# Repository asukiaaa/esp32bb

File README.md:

# ESP32BB
A kicad project for ESP-WROOM-32 and breadboard.

[schema](/docs/esp32bb.pdf)

# Driver
This board uses CP2102 for serial communication.
For mac and windiws user, please install the following driver.
Linux supports cp2102 defaul, so linux user does not need any driver.

[CP210x USB to UART Bridge VCP Drivers](http://www.silabs.com/products/development-tools/software/usb-to-uart-bridge-vcp-drivers)

# Shop
[trial stacks](https://trialstacks.base.ec/items/6243312)

# Components
- [esp-wroop-32](http://akizukidenshi.com/catalog/g/gM-11647/)
- [Hirose-microB-USB](http://akizukidenshi.com/catalog/g/gC-05254/)
- [Diode](http://akizukidenshi.com/catalog/g/gI-05951/)
- [transistor MMBT3904](http://akizukidenshi.com/catalog/g/gI-05969/)
- [switch SKRPACE010](http://akizukidenshi.com/catalog/g/gP-06185/)
- [100uf 1206 condensor](http://akizukidenshi.com/catalog/g/gP-08260/)
- [10uf 0603 condensor](http://akizukidenshi.com/catalog/g/gP-07768/)
- [0.1uf 0603 condensor](http://akizukidenshi.com/catalog/g/gP-04940/)
- [1nf (1000pf) 0603 condensor](http://akizukidenshi.com/catalog/g/gP-09285/)
- [10k 0603 registor](http://akizukidenshi.com/catalog/g/gR-06103/)
- [led](http://akizukidenshi.com/catalog/g/gI-06417/)
- [Pin socket](http://akizukidenshi.com/catalog/g/gC-05779/)
- Bread board: [akizuki](http://akizukidenshi.com/catalog/g/gP-05158/) or [aliexpress](https://www.aliexpress.com/item/SYB-170-Mini-Prototype-Experiment-Test-Breadboard-Board-Tie-points-170-Tie-points-35-47-8/32595538101.html?spm=2114.13010608.0.0.nAnEqS)
- [CP2102](https://www.aliexpress.com/item/5pcs-Free-shipping-SILABS-CP2102-GMR-CP2102-QFN-28-offen-use-laptop-chip-100-new-original/32503317767.html?spm=2114.13010608.0.0.PUEIRm)
- [NCP1117ST33T3G](https://www.aliexpress.com/item/Free-Shipping-NCP1117ST33T3G-NCP1117-3-3V-linear-regulator-SOT-223-package/32244660148.html?spm=2114.13010608.0.0.PUEIRm)

# Footprints
- [ESP32-kiCAD-Footprints](https://github.com/adamjvr/ESP32-kiCAD-Footprints)
- [switch: SKRPACE010.kicad_mod](https://github.com/nosuz/kicad-lib/blob/master/module.pretty/SKRPACE010.kicad_mod)

# Programming software tools
ESP32BB is a ESP-WROOM-32 breakout board so you can write your own program by usinig the following tools.

- [espressif/arduino-esp32](https://github.com/espressif/arduino-esp32)
- [espressif/esp-idf](https://github.com/espressif/esp-idf)
- [Mongoose OS](https://mongoose-os.com/)

# License
MIT

# References
- [ESP32-Core-Board-V2_sch.pdf](http://akizukidenshi.com/download/ds/espressifsystems/ESP32-Core-Board-V2_sch.pdf)
- [esp_wroom_32_datasheet_en.pdf](https://espressif.com/sites/default/files/documentation/esp_wroom_32_datasheet_en.pdf)
- [Enginursday: First Impressions of the ESP32](https://www.sparkfun.com/news/2017)
- [ESP32 Development Board with TELEC Memorial photograph](https://macsbug.wordpress.com/2016/12/12/esp32-development-board-with-telec-memorial-photograph/)
- [DS_FT232R](http://www.ftdichip.com/Support/Documents/DataSheets/ICs/DS_FT232R.pdf)
- [SparkFun FTDI Basic Breakout - 3.3V](https://www.sparkfun.com/products/9873)
- [Sehematic of SparkFun FTDI Basic Breakout - 3.3V](http://cdn.sparkfun.com/datasheets/BreakoutBoards/FTDI%20Basic-v22-3.3V.pdf)
- [esp32-thing.sch](https://cdn.sparkfun.com/assets/learn_tutorials/5/0/7/esp32-thing-schematic.pdf)
- [The Internet of Things with ESP32](http://esp32.net/)
- [ESP-WROVER-KIT_SCH-2.pdf](https://dl.espressif.com/dl/schematics/ESP-WROVER-KIT_SCH-2.pdf)
- [ESP32-EVB_Rev_A.pdf](https://github.com/OLIMEX/ESP32-EVB/blob/master/HARDWARE/REV-A/ESP32-EVB_Rev_A.pdf)

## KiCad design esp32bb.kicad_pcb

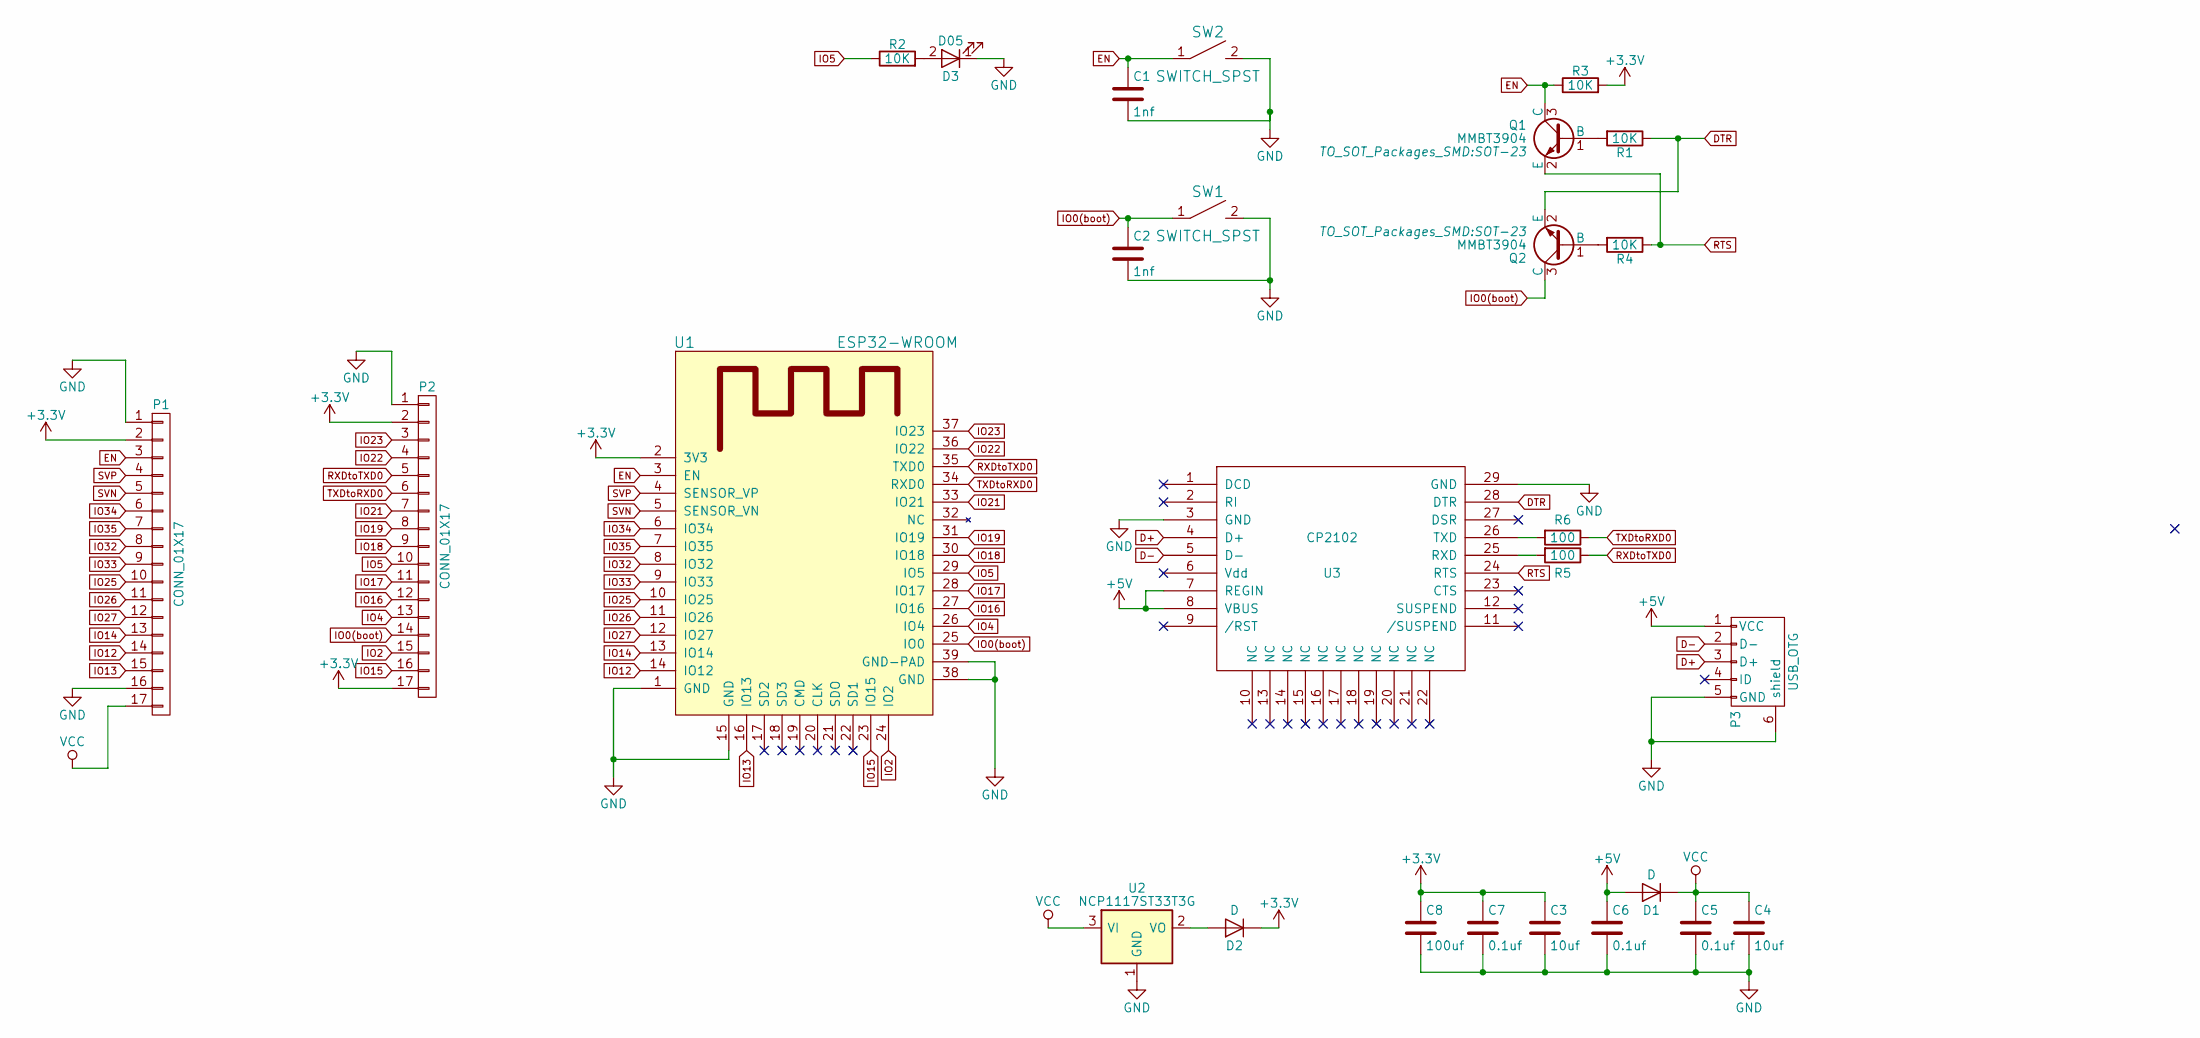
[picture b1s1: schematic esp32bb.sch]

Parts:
C1, C2: 1nf; C_0603
C3, C4: 10uf; C_0603
C5, C6, C7: 0.1uf; C_0603
C8: 100uf; C_1206
D1, D2: D; D_0805
D3: D05; LED_0603
P1, P2: CONN_01X17; Pin_Header_Straight_1x17_Pitch2.54mm
P3: USB_OTG; USB_MICRO_B-HIROSE-ZX62R-B-5P
Q1, Q2: MMBT3904; SOT-23
R1, R2, R3, R4: 10K; R_0603
R5, R6: 100; R_0603
SW1, SW2: SWITCH_SPST; SKRPACE010
U1: ESP32-WROOM
U2: NCP1117ST33T3G; SOT-223
U3: CP2102; QFN-28-1EP_5x5mm_Pitch0.5mm

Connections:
+3V3: C3.1, C7.1, C8.1, D2.1 (K), P1.2, P2.2, P2.17, R3.2, U1.2 (3V3)
+5V: C6.1, D1.2 (A), P3.1 (VCC), U3.7 (REGIN), U3.8 (VBUS); also elsewhere on the board
D+: P3.3 (D+), U3.4 (D+); also elsewhere on the board
D-: P3.2 (D-), U3.5 (D-); also elsewhere on the board
DTR: Q2.2 (E), R1.1, U3.28 (DTR)
EN: C1.1, P1.3, Q1.3 (C), R3.1, SW2.1, U1.3 (EN)
GND: C1.2, C2.2, C3.2, C4.2, C5.2, C6.2, C7.2, C8.2, D3.1 (K), P1.1, P1.16, P2.1, P3.5 (GND), P3.6 (shield), SW1.2, SW2.2, U1.1 (GND), U1.15 (GND), U1.38 (GND), U1.39 (GND-PAD), U2.1 (GND), U3.3 (GND), U3.29 (GND); also elsewhere on the board
IO0(boot): C2.1, P2.14, Q2.3 (C), SW1.1, U1.25 (IO0)
IO2: P2.15, U1.24 (IO2)
IO4: P2.13, U1.26 (IO4)
IO5: P2.10, R2.1, U1.29 (IO5)
IO12: P1.14, U1.14 (IO12)
IO13: P1.15, U1.16 (IO13)
IO14: P1.13, U1.13 (IO14)
IO15: P2.16, U1.23 (IO15)
IO16: P2.12, U1.27 (IO16)
IO17: P2.11, U1.28 (IO17)
IO18: P2.9, U1.30 (IO18)
IO19: P2.8, U1.31 (IO19)
IO21: P2.7, U1.33 (IO21)
IO22: P2.4, U1.36 (IO22)
IO23: P2.3, U1.37 (IO23)
IO25: P1.10, U1.10 (IO25)
IO26: P1.11, U1.11 (IO26)
IO27: P1.12, U1.12 (IO27)
IO32: P1.8, U1.8 (IO32)
IO33: P1.9, U1.9 (IO33)
IO34: P1.6, U1.6 (IO34)
IO35: P1.7, U1.7 (IO35)
unnamed: D2.2 (A), U2.2 (VO)
unnamed: D3.2 (A), R2.2
unnamed 31: P3.4 (ID); also elsewhere on the board
unnamed: Q1.1 (B), R1.2
unnamed: Q2.1 (B), R4.2
unnamed: R5.2, U3.25 (RXD)
unnamed: R6.2, U3.26 (TXD)
RTS: Q1.2 (E), R4.1, U3.24 (RTS)
RXDtoTXD0: P2.5, R5.1, U1.35 (TXD0)
SVN: P1.5, U1.5 (SENSOR_VN)
SVP: P1.4, U1.4 (SENSOR_VP)
TXDtoRXD0: P2.6, R6.1, U1.34 (RXD0)
VCC: C4.1, C5.1, D1.1 (K), P1.17, U2.3 (VI)

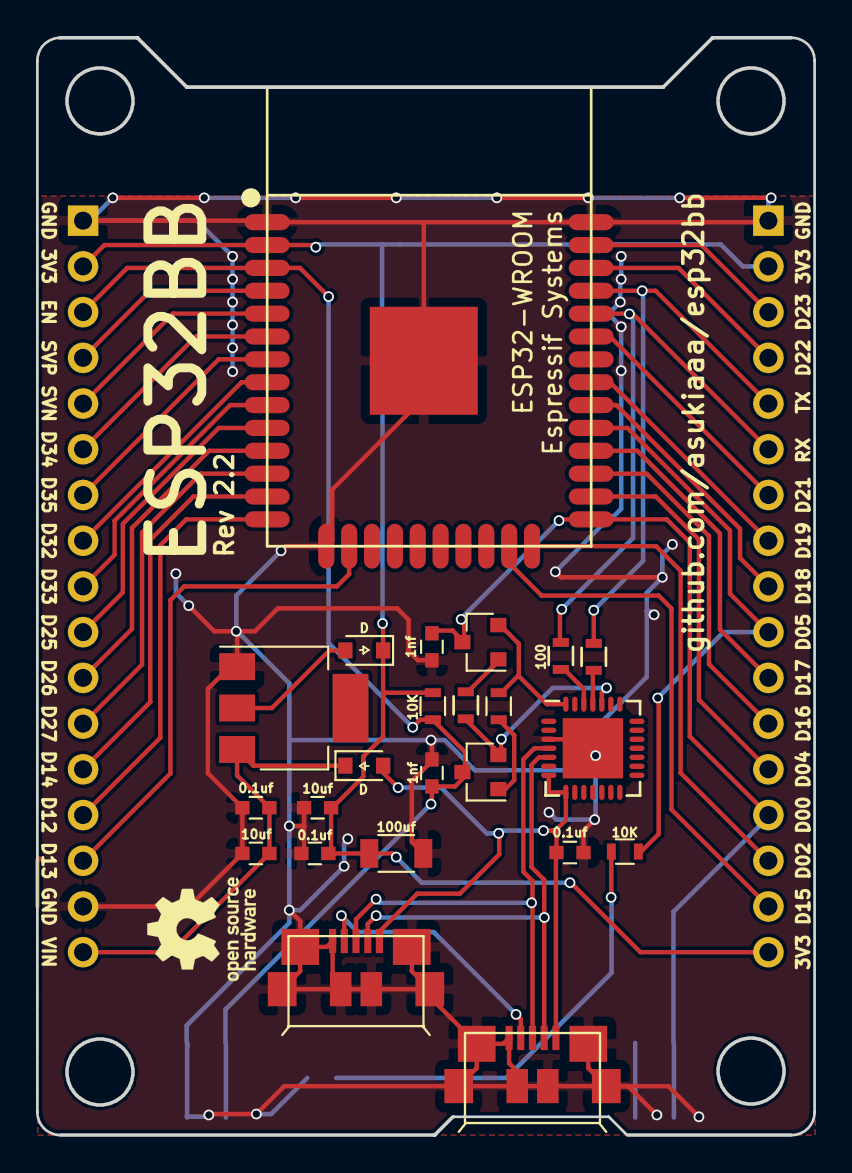
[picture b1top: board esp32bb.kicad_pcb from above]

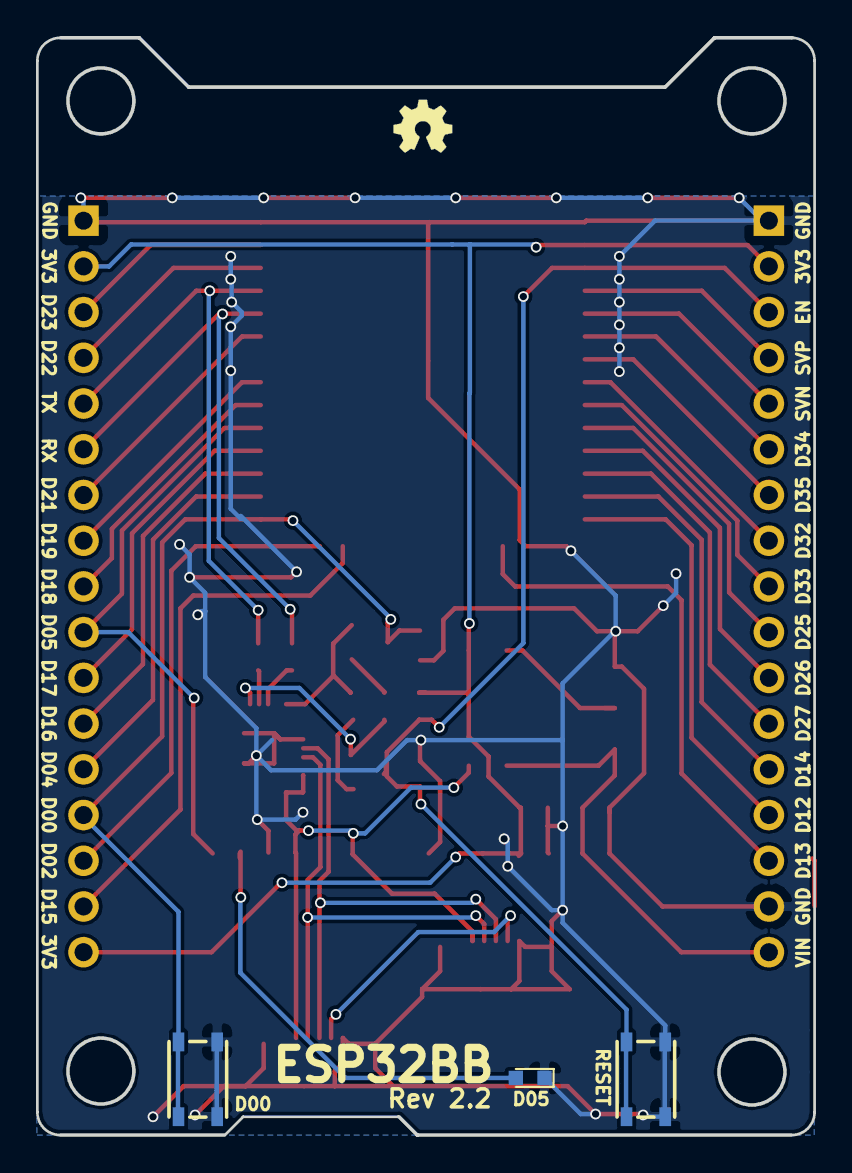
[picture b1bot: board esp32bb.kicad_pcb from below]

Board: 2 copper layers, 43.1 x 61.0 mm, 28 parts (5 on the bottom side), 42 nets.

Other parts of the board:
P3#2: USB_OTG; USB_MICRO_B-HIROSE-ZX62R-B-5P

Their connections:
+5V: P3#2.1; also elsewhere on the board
D+: P3#2.3; also elsewhere on the board
D-: P3#2.2; also elsewhere on the board
GND: P3#2.5, P3#2.6; also elsewhere on the board
unnamed 31: P3#2.4; also elsewhere on the board

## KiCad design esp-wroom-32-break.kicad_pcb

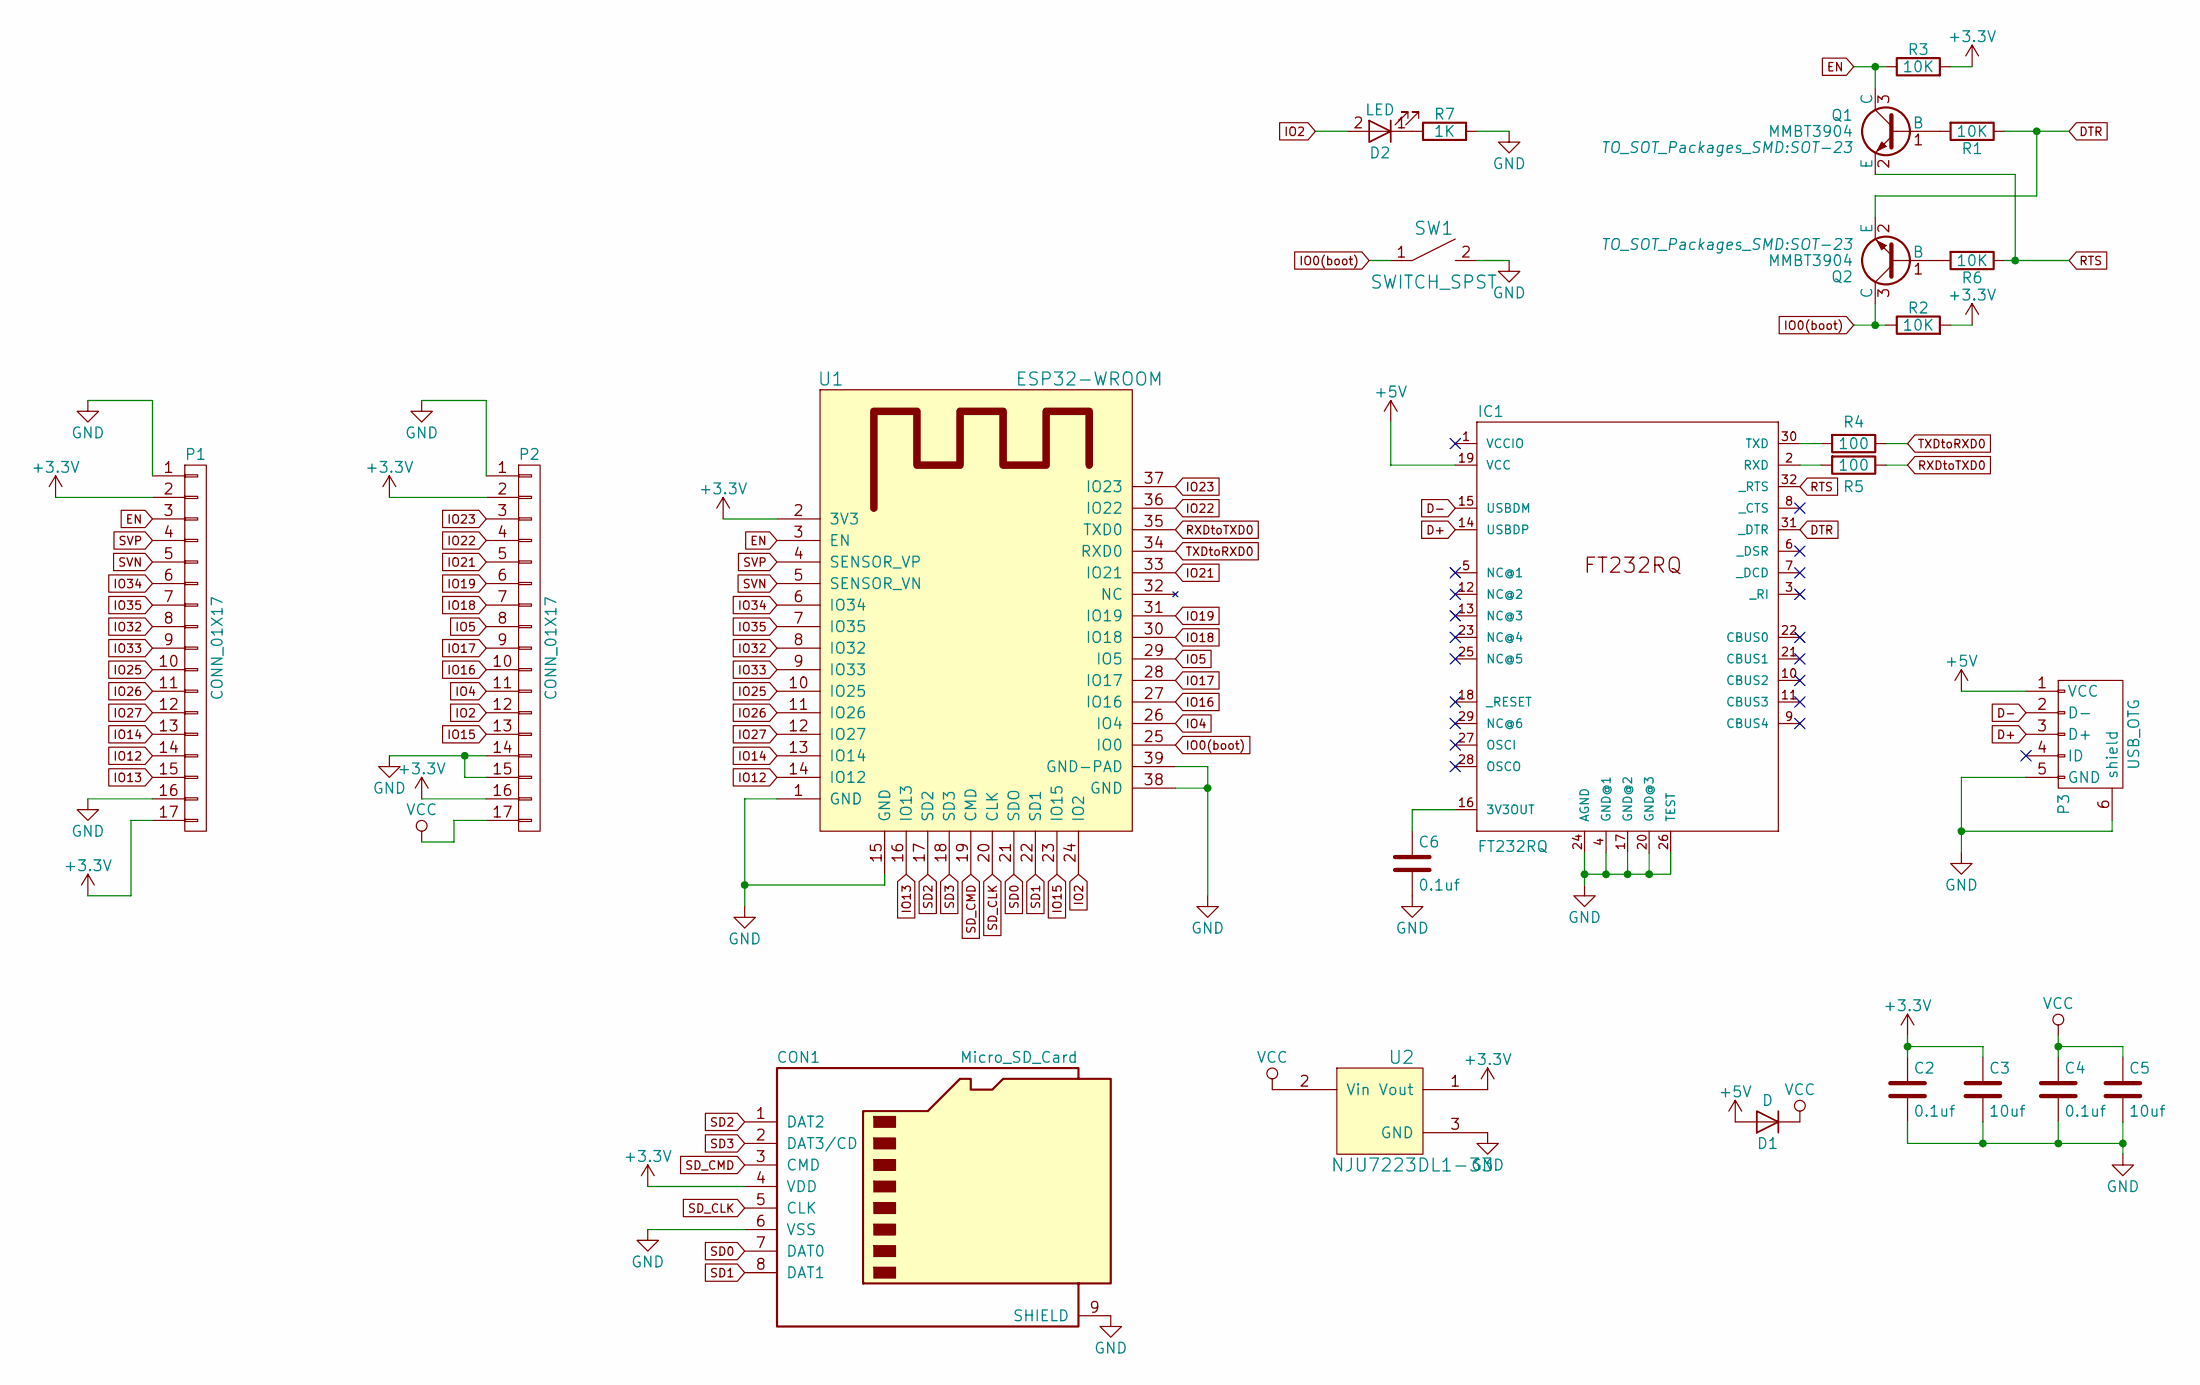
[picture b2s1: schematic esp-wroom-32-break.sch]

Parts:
C2, C4, C6: 0.1uf; C_0603
C3, C5: 10uf; C_0603
CON1: Micro_SD_Card; microSD_Card_Receptacle_Hirose_DM3AT-SF-PEJM5
D1: D; D_0805
D2: LED; LED_0603
IC1: FT232RQ; ft232rq
P1, P2: CONN_01X17; Pin_Header_Straight_1x17_Pitch2.54mm
P3: USB_OTG; USB_MICRO_B-HIROSE-ZX62R-B-5P
Q1, Q2: MMBT3904; SOT-23
R1, R2, R3, R6: 10K; R_0603
R4, R5: 100; R_0603
R7: 1K; R_0603
SW1: SWITCH_SPST; SKRPACE010
U1: ESP32-WROOM
U2: NJU7223DL1-33; TO-252-2Lead

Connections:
+3V3: C2.1, C3.1, CON1.4 (VDD), P1.2, P1.17, P2.2, P2.16, R2.2, R3.2, U1.2 (3V3), U2.1 (Vout)
+5V: D1.2 (A), IC1.19 (VCC), P3.1 (VCC)
D+: IC1.14 (USBDP), P3.3 (D+)
D-: IC1.15 (USBDM), P3.2 (D-)
DTR: IC1.31 (_DTR), Q2.2 (E), R1.1
EN: P1.3, Q1.3 (C), R3.1, U1.3 (EN)
GND: C2.2, C3.2, C4.2, C5.2, C6.2, CON1.6 (VSS), CON1.9 (SHIELD), IC1.4 (GND@1), IC1.17 (GND@2), IC1.20 (GND@3), IC1.24 (AGND), IC1.26 (TEST), P1.1, P1.16, P2.1, P2.14, P2.15, P3.5 (GND), P3.6 (shield), R7.2, SW1.2, U1.1 (GND), U1.15 (GND), U1.38 (GND), U1.39 (GND-PAD), U2.3 (GND)
IO0(boot): Q2.3 (C), R2.1, SW1.1, U1.25 (IO0)
IO2: D2.2 (A), P2.12, U1.24 (IO2)
IO4: P2.11, U1.26 (IO4)
IO5: P2.8, U1.29 (IO5)
IO12: P1.14, U1.14 (IO12)
IO13: P1.15, U1.16 (IO13)
IO14: P1.13, U1.13 (IO14)
IO15: P2.13, U1.23 (IO15)
IO16: P2.10, U1.27 (IO16)
IO17: P2.9, U1.28 (IO17)
IO18: P2.7, U1.30 (IO18)
IO19: P2.6, U1.31 (IO19)
IO21: P2.5, U1.33 (IO21)
IO22: P2.4, U1.36 (IO22)
IO23: P2.3, U1.37 (IO23)
IO25: P1.10, U1.10 (IO25)
IO26: P1.11, U1.11 (IO26)
IO27: P1.12, U1.12 (IO27)
IO32: P1.8, U1.8 (IO32)
IO33: P1.9, U1.9 (IO33)
IO34: P1.6, U1.6 (IO34)
IO35: P1.7, U1.7 (IO35)
unnamed: C6.1, IC1.16 (3V3OUT)
unnamed: D2.1 (K), R7.1
unnamed: IC1.2 (RXD), R5.2
unnamed: IC1.30 (TXD), R4.2
unnamed: Q1.1 (B), R1.2
unnamed: Q2.1 (B), R6.2
RTS: IC1.32 (_RTS), Q1.2 (E), R6.1
RXDtoTXD0: R5.1, U1.35 (TXD0)
SD0: CON1.7 (DAT0), U1.21 (SDO)
SD1: CON1.8 (DAT1), U1.22 (SD1)
SD2: CON1.1 (DAT2), U1.17 (SD2)
SD3: CON1.2 (DAT3/CD), U1.18 (SD3)
SD_CLK: CON1.5 (CLK), U1.20 (CLK)
SD_CMD: CON1.3 (CMD), U1.19 (CMD)
SVN: P1.5, U1.5 (SENSOR_VN)
SVP: P1.4, U1.4 (SENSOR_VP)
TXDtoRXD0: R4.1, U1.34 (RXD0)
VCC: C4.1, C5.1, D1.1 (K), P2.17, U2.2 (Vin)

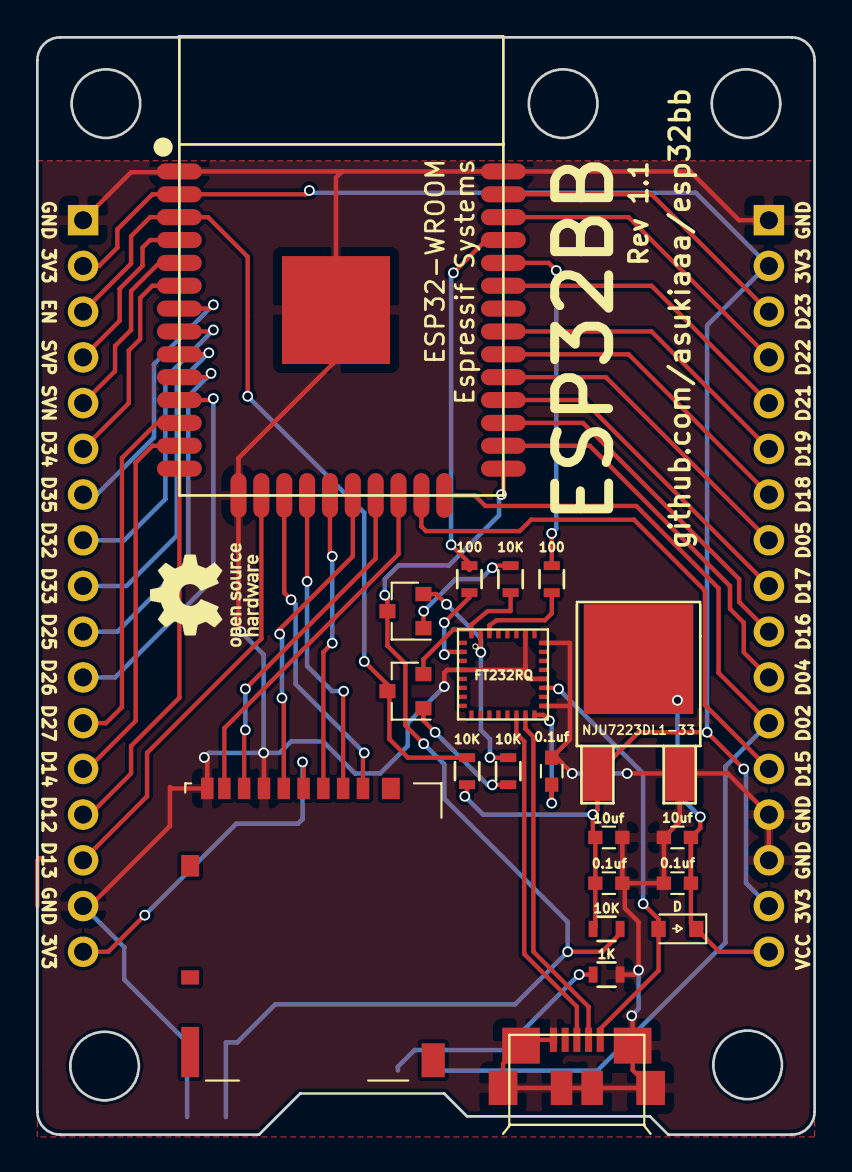
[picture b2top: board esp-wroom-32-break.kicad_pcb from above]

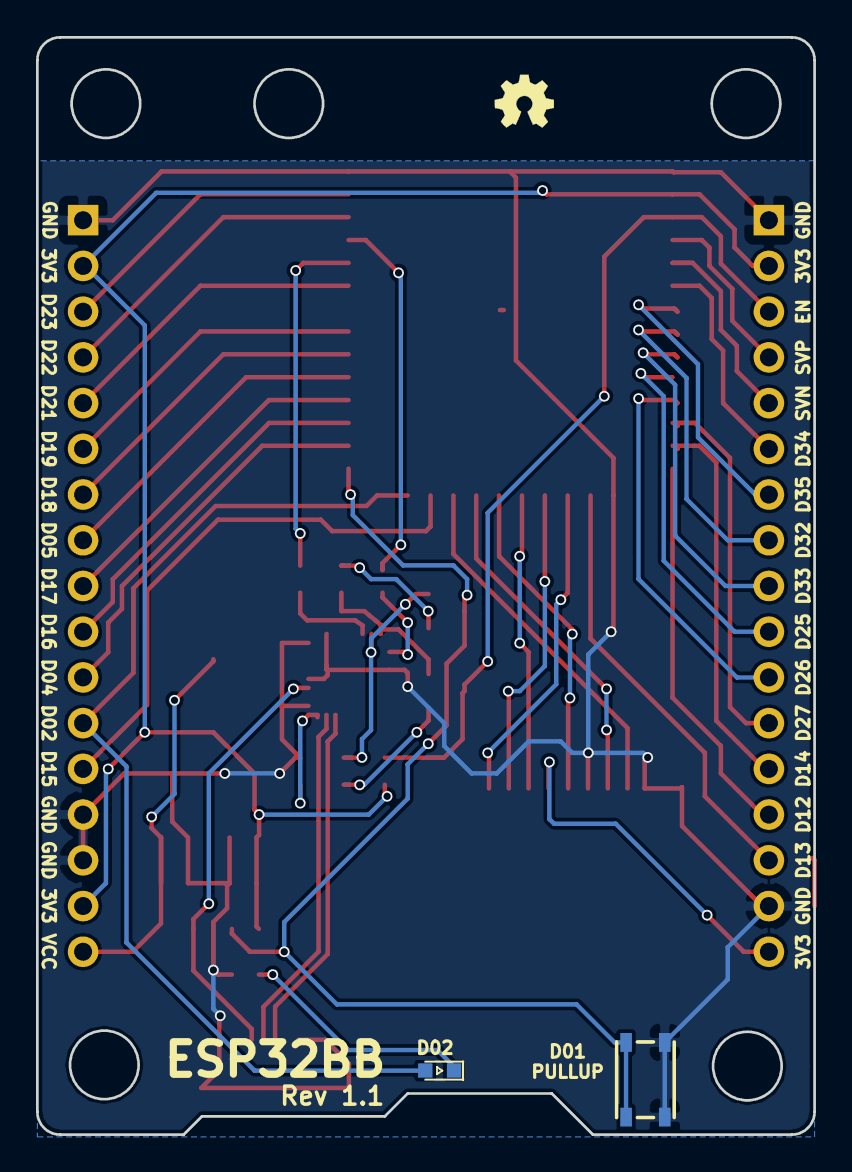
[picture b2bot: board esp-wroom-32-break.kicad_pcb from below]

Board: 2 copper layers, 43.2 x 61.0 mm, 24 parts (2 on the bottom side), 47 nets.

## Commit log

2017-01-03 Add link for datasheet about FT232R
2017-01-04 Add link about sparkfun FTDI breakout board
2017-01-05 Put wroom-32 and ftdi to schema
2017-01-07 Change files place
2017-02-03 Update schema with using 18 pins connectors etc
2017-02-04 Add component info to readme
2017-02-05 Assign component footprints and generated net file
2017-02-06 Put footprints
2017-02-06 Created revision 1.0 pcb
2017-02-08 Add plot files to order to elecrow
2017-02-10 Add components info to readme
2017-02-17 Add a svg file as a silk
2017-02-18 Correct pin name on back silk
2017-02-18 Add modification plan to readme
2017-02-18 Change to 17 pins socket and remove redundant condensors
2017-02-18 Remove plan to replace ftdi chip because it is no problem
2017-02-19 Update schema and netlist with adding auto reset circuit
2017-02-20 Put footprints for rev1.1
2017-02-20 Change led and silk layout
2017-02-20 Update plots to order for elecrow
2017-02-25 Add reference links to readme
2017-02-25 Add registers to pull up SD signals and reset button etc
2017-02-27 Remove modification plan
2017-03-01 Add software info to readme
2017-03-01 Rename project name to esp32bb
2017-03-02 Update silk
2017-03-02 Prepare docs for releasing rev1.2
2017-03-03 Add RX TX to headers
2017-03-03 Show component number on fab layer
2017-03-04 Update hole position
2017-03-04 Update plots for new hole position
2017-03-05 Add mongoose os to software tools
2017-03-06 Change holls size and position and add dimension
2017-03-07 Add size image to readme
2017-03-07 Add keep out area for SD card holder
2017-03-08 Update plots for rev1.4 with setting keepout area for SD card holder
2017-03-10 Update schema pdf
2017-03-10 Recover lost silk for register
2017-03-11 Add pin socket and bread board info to readme
2017-03-13 Add foot_plate as a frame
2017-03-14 Add bottom cover
2017-03-15 Add bottom_cover_through
2017-03-18 Update schema to use CP2102 and NCP1117DT33 and remove SD card holder
2017-03-19 Update plots to order rev2.0 PCB
2017-03-23 Add CP2102 and NCP111 to components list in readme
2017-03-28 Correct and update schema and pcb for rev2.1
2017-03-29 Change outline of bottom_cover_through
2017-03-29 Move position of plots.zip into elecrow directory
2017-03-29 Add requirements file for rev2.1 to order PCBA service for elecrow
2017-04-18 Back hirose micro-USB to readme and bom
2017-04-18 Correct led label to D05
2017-04-19 Modify ground zone
2017-04-20 Correct label of led on schema
2017-04-21 Add diode for 3v3 and modify label for registers and condensors
2017-04-30 Add release_note
2017-04-30 Correct typo in readme
2017-05-02 Change hole position on bottom cover
2017-05-03 Add shop info
2017-05-04 Add image
2017-05-05 Update image
2017-05-07 Correct path for image
2017-05-28 Add driver info
2019-01-04 Create main_pcb directory
2019-01-04 Add frame data
2019-01-05 Add bottom pcb
2019-01-18 Add spacer_pcb
2019-01-18 Correct size of bottom pcb
